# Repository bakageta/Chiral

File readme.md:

# Chiral

An ambidextrous numpad based on pluis9's [Helix](https://github.com/MakotoKurauchi/helix).

## Layout

## Changelog

v0.1 - Proto PCBs ordered for testing.

v0.2 - Organized footprints used, initial silkscreen work

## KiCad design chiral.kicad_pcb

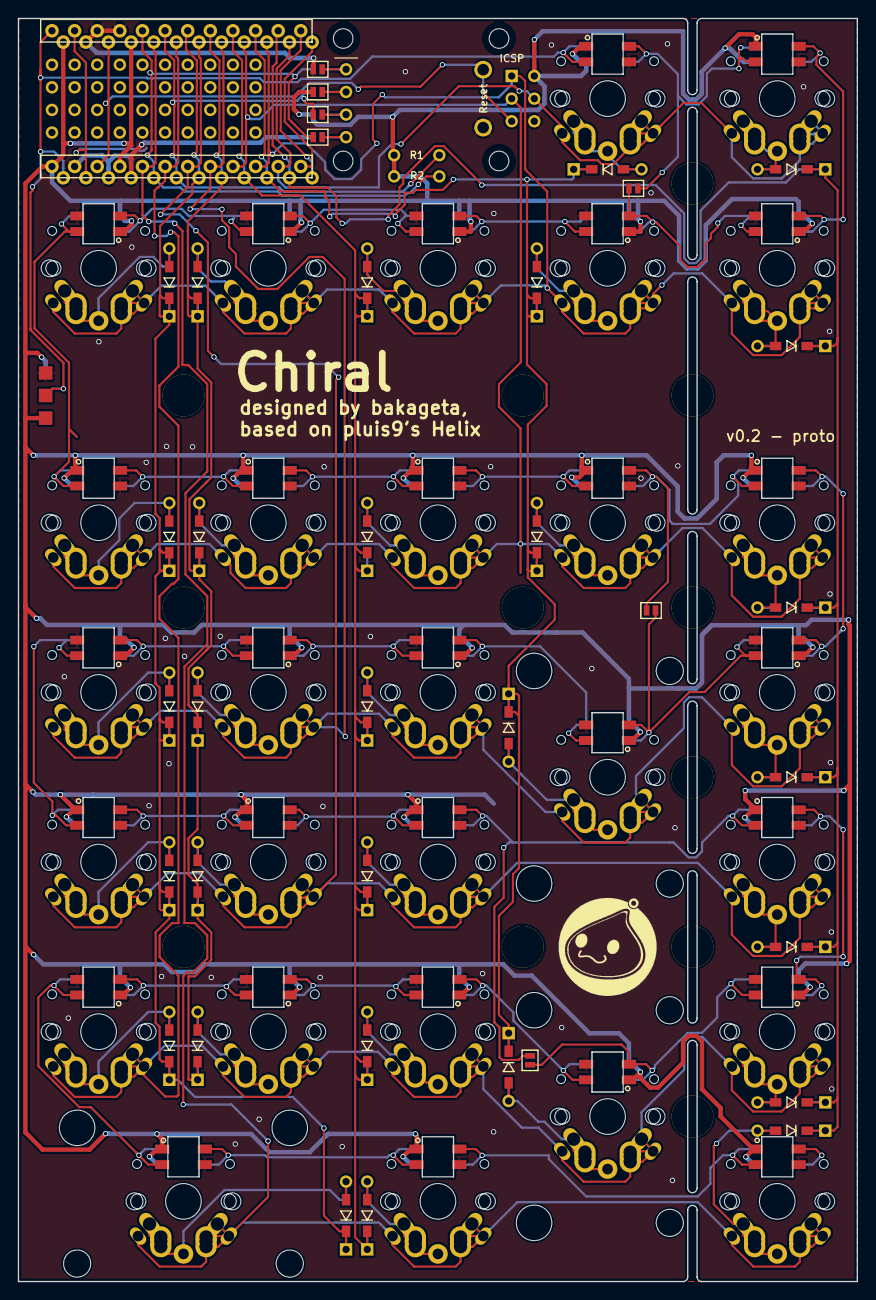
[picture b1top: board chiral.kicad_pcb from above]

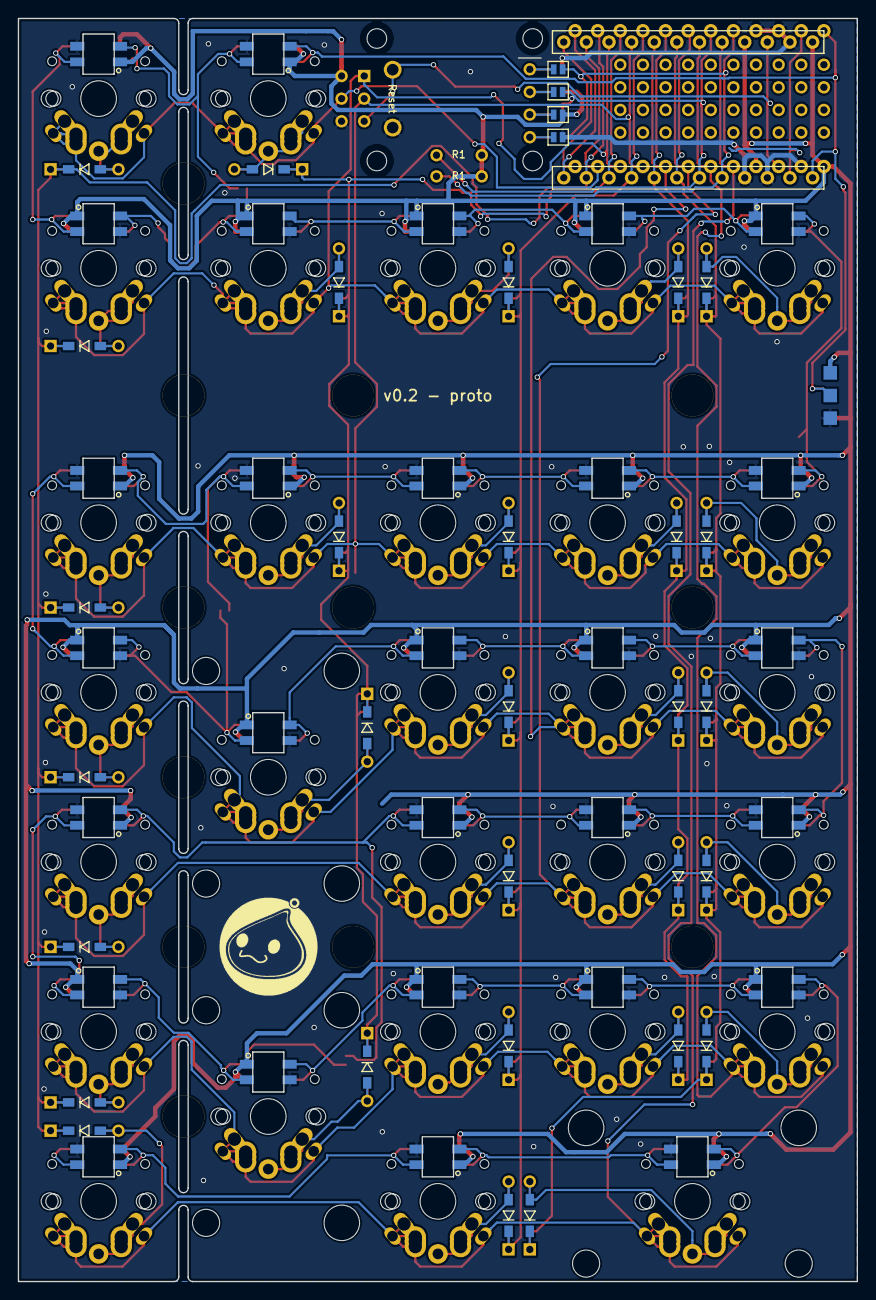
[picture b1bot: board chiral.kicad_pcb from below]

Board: 2 copper layers, 94.2 x 141.8 mm, 135 parts (5 on the bottom side), 79 nets.

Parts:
B1, B8: EdgeCut; Break_Cut_Edge
B2, B4, B5, B6, B7: EdgeCut; Break_Cut_MX100
B3: EdgeCut; Break_Cut_MX150
D1, D2, D3, D4, D5, D6, D7, D8, D9, D10, D11, D12, D13, D14, D15, D16, D17, D18, D19, D20, D21, D22, D23, D24, D25, D26, D27, D28, D29: D; D3_TH_SMD
H1: Cooling Holes; PinHeader_4x10_P2.54mm
H2, H3, H4, H5: M2; HOLE_M2
H6, H7, H8, H9, H10, H11, H12, H13, H14, H15, H16, H17: 4.7mm; HOLE_4.7mm
JP1, JP2, JP3: JP2; Jumper
JP4, JP11: GND; Jumper
JP5, JP10: VCC; Jumper
JP6, JP9: SCL; Jumper
JP7, JP8: SDA; Jumper
LOGO1, LOGO1#2: MISC; LOGO_poring
MCU1: ProMicro; ProMicro_Double
P1: OLED; MY_SIL-4
P2: LED; StripLED_rev
P3: ICSP; MY_SIL-2x3
R1, R2: R; R2
SW1, SW2, SW3, SW4, SW5, SW6, SW7, SW8, SW9, SW10, SW11, SW12, SW13, SW14, SW15, SW16, SW17, SW18, SW19, SW20, SW21, SW22, SW23, SW24, SW25, SW26, SW27, SW28, SW29: SW_PUSH; MX_ALPS_PG1350_noLed
SW30: Reset; SW_3.5x6.0_TH
SW?: MX_PCB_STAB_200
SW?#2, SW?#3: MX_PCB_STAB_200
U1, U2, U8, U9, U10, U11, U12, U18, U19, U20, U21, U27, U28, U29: SK6812mini; SK6812MINI_MX_Offset_180
U3, U4, U5, U6, U7, U13, U14, U15, U16, U17, U22, U23, U24, U25, U26: SK6812mini; SK6812MINI_MX_Offset

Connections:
/RESET: MCU1.22, P3.5, SW30.2
/SCL: JP6.1, JP9.1, MCU1.6, R1.2
/SDA: JP7.1, JP8.1, MCU1.5, R2.2
GND: JP4.1, JP11.1, MCU1.3, MCU1.4, MCU1.23, P2.3, P3.6, SW30.1, U1.2, U2.2, U3.2, U4.2, U5.2, U6.2, U7.2, U8.2, U9.2, U10.2, U11.2, U12.2, U13.2, U14.2, U15.2, U16.2, U17.2, U18.2, U19.2, U20.2, U21.2, U22.2, U23.2, U24.2, U25.2, U26.2, U27.2, U28.2, U29.2
LED: MCU1.1, P2.2, U1.3
unnamed: D1.2, SW1.2
unnamed: D2.2, SW2.2
unnamed: D3.2, SW3.2
unnamed: D4.2, SW4.2
unnamed: D5.2, SW5.2
unnamed: D6.2, SW6.2
unnamed: D7.2, SW7.2
unnamed: D8.2, SW8.2
unnamed: D9.2, SW9.2
unnamed: D10.2, SW10.2
unnamed: D11.2, SW11.2
unnamed: D12.2, SW12.2
unnamed: D13.2, SW13.2
unnamed: D14.2, SW14.2
unnamed: D15.2, SW15.2
unnamed: D16.2, SW16.2
unnamed: D17.2, SW17.2
unnamed: D18.2, SW18.2
unnamed: D19.2, SW19.2
unnamed: D20.2, SW20.2
unnamed: D21.2, SW21.2
unnamed: D22.2, SW22.2
unnamed: D23.2, SW23.2
unnamed: D24.2, SW24.2
unnamed: D25.2, SW25.2
unnamed: D26.2, SW26.2
unnamed: D27.2, SW27.2
unnamed: D28.2, SW28.2
unnamed: D29.2, SW29.2
unnamed: JP1.1, U1.1, U2.3
unnamed: JP1.2, U6.3, U7.1
unnamed: JP2.1, U11.1, U12.3
unnamed: JP2.2, U16.3, U17.1
unnamed: JP3.1, U20.1, U21.3
unnamed: JP3.2, U25.3, U26.1
unnamed: JP4.2, JP8.2, P1.1
unnamed: JP5.2, JP9.2, P1.2
unnamed: JP6.2, JP10.2, P1.3
unnamed: JP7.2, JP11.2, P1.4
unnamed: U2.1, U7.3
unnamed: U3.1, U8.3
unnamed: U3.3, U4.1
unnamed: U4.3, U5.1
unnamed: U5.3, U6.1
unnamed: U8.1, U9.3
unnamed: U10.1, U11.3
unnamed: U9.1, U10.3
unnamed: U12.1, U17.3
unnamed: U13.1, U18.3
unnamed: U13.3, U14.1
unnamed: U14.3, U15.1
unnamed: U15.3, U16.1
unnamed: U18.1, U19.3
unnamed: U19.1, U20.3
unnamed: U21.1, U26.3
unnamed: U22.1, U27.3
unnamed: U22.3, U23.1
unnamed: U23.3, U24.1
unnamed: U24.3, U25.1
unnamed: U27.1, U28.3
unnamed: U28.1, U29.3
VCC: JP5.1, JP10.1, MCU1.21, MCU1.24, P2.1, P3.2, R1.1, R2.1, U1.4, U2.4, U3.4, U4.4, U5.4, U6.4, U7.4, U8.4, U9.4, U10.4, U11.4, U12.4, U13.4, U14.4, U15.4, U16.4, U17.4, U18.4, U19.4, U20.4, U21.4, U22.4, U23.4, U24.4, U25.4, U26.4, U27.4, U28.4, U29.4
col0: D3.1, D8.1, D13.1, D18.1, D22.1, D27.1, MCU1.7
col1: D4.1, D9.1, D14.1, D19.1, D23.1, MCU1.8
col2: D5.1, D10.1, D15.1, D20.1, D24.1, D28.1, MCU1.9
col3: D1.1, D6.1, D11.1, D16.1, D25.1, MCU1.10
col4: D2.1, D7.1, D12.1, D17.1, D21.1, D26.1, D29.1, MCU1.11
row0: MCU1.14, P3.4, SW1.1, SW2.1
row1: MCU1.15, P3.1, SW3.1, SW4.1, SW5.1, SW6.1, SW7.1
row2: MCU1.16, P3.3, SW8.1, SW9.1, SW10.1, SW11.1, SW12.1
row3: MCU1.17, SW13.1, SW14.1, SW15.1, SW16.1, SW17.1
row4: MCU1.18, SW18.1, SW19.1, SW20.1, SW21.1
row5: MCU1.19, SW22.1, SW23.1, SW24.1, SW25.1, SW26.1
row6: MCU1.20, SW27.1, SW28.1, SW29.1

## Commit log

2018-09-19 v0.2 - Initial upload
